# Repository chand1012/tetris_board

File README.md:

# Tetris Circuit Board
schemiatic and arduino file for a credit card sized tetris board.
## To do ##
- ~~Upload the .ino file~~
- add way to program atmega328p or add DIP Socket
- Finish the ~~Gerber~~ BOM File (Add all components to list, [this](https://octopart.com/bom-tool) should help.)
- have some printed and assembled by [Seeed](https://www.seeedstudio.com/fusion_pcb.html)
- figure out the switch you want to use on the boards
### Other assembly options ###
- Order the PCB from [Seeed](https://www.seeedstudio.com/fusion_pcb.html), assemble it yourself.

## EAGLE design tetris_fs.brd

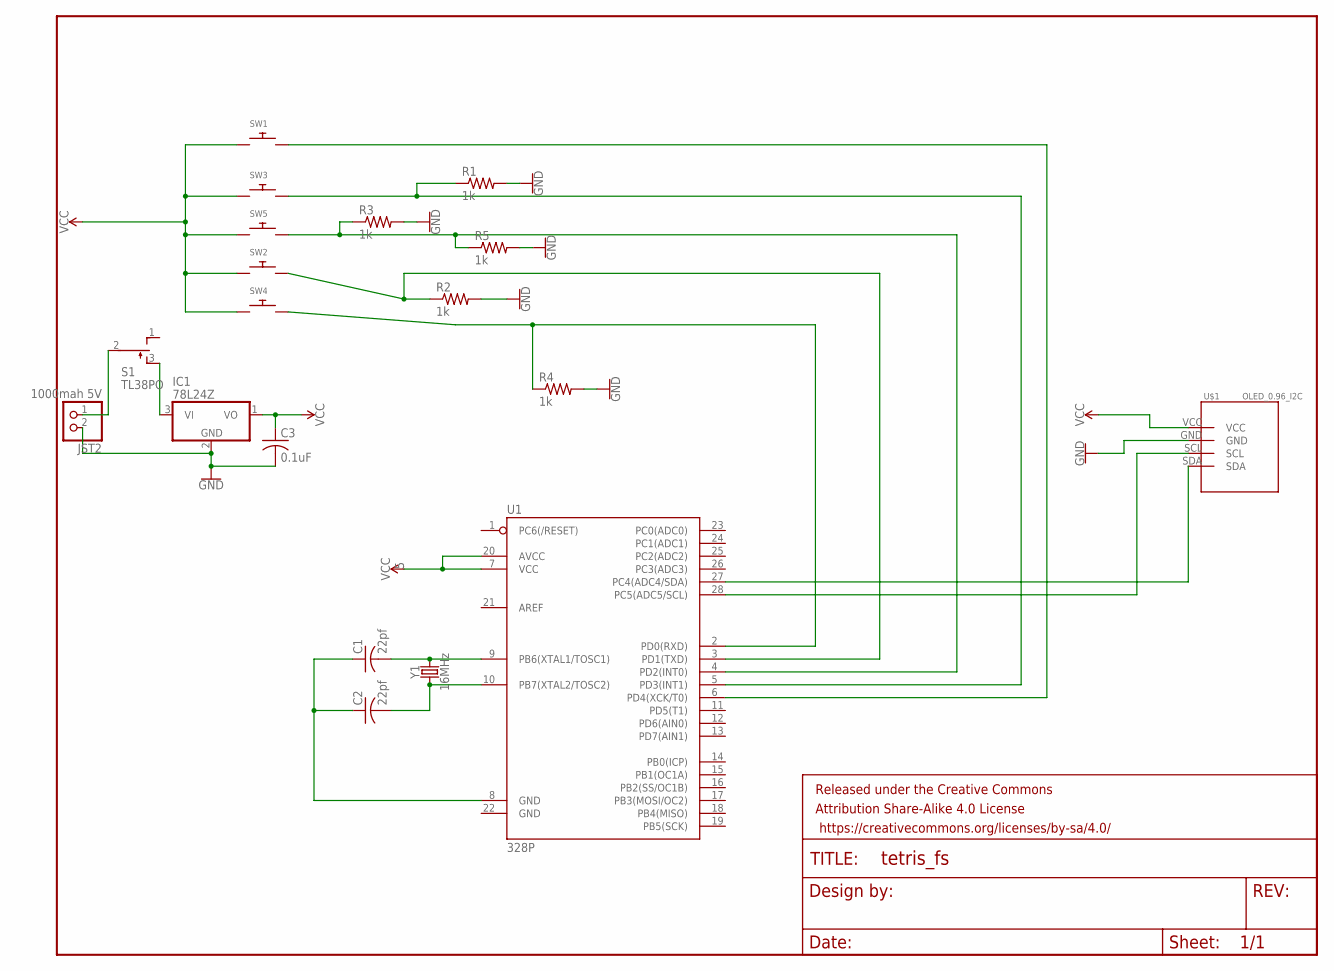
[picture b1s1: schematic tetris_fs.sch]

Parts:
C1, C2: 22pf; C050-030X075
C3: 0.1uF; C050-030X075
FRAME1: FRAME-LETTERNO_PACKAGE; DUMMY
IC1: 78L24Z; TO92
JST2: 1000mah 5V; JST-PH-2-SMT-RA
R1, R2, R3, R4, R5: 1k; 0805-THM
S1: TL38PO; TL3XPO
SW1, SW2, SW3, SW4, SW5: SWITCH_PUSHBUTTONC&K_KSS; BTN_CK_KSS
U1: 328P; DIP28
U$1: OLED_0.96_I2C
Y1: 16MHz; HC49US

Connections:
GND: C3.2, IC1.2 (GND), JST2.2 (1), R1.2, R2.2, R3.2, R4.2, R5.2, U$1.GND
unnamed: SW1.P$2, U1.6 (PD4(XCK/T0))
unnamed: R1.1, SW3.P$2, U1.5 (PD3(INT1))
unnamed: R3.1, R5.1, SW5.P$2, U1.4 (PD2(INT0))
unnamed: R2.1, SW2.P$2, U1.3 (PD1(TXD))
unnamed: R4.1, SW4.P$2, U1.2 (PD0(RXD))
unnamed: C1.2, U1.9 (PB6(XTAL1/TOSC1)), Y1.2
unnamed: C2.2, U1.10 (PB7(XTAL2/TOSC2)), Y1.1
unnamed: C1.1, C2.1, U1.8 (GND)
unnamed: JST2.1 (2), S1.2
unnamed: U1.27 (PC4(ADC4/SDA)), U$1.SDA
unnamed: U1.28 (PC5(ADC5/SCL)), U$1.SCL
unnamed: IC1.3 (VI), S1.3 (S)
VCC: C3.1, IC1.1 (VO), SW1.P$1, SW2.P$1, SW3.P$1, SW4.P$1, SW5.P$1, U1.7 (VCC), U1.20 (AVCC), U$1.VCC

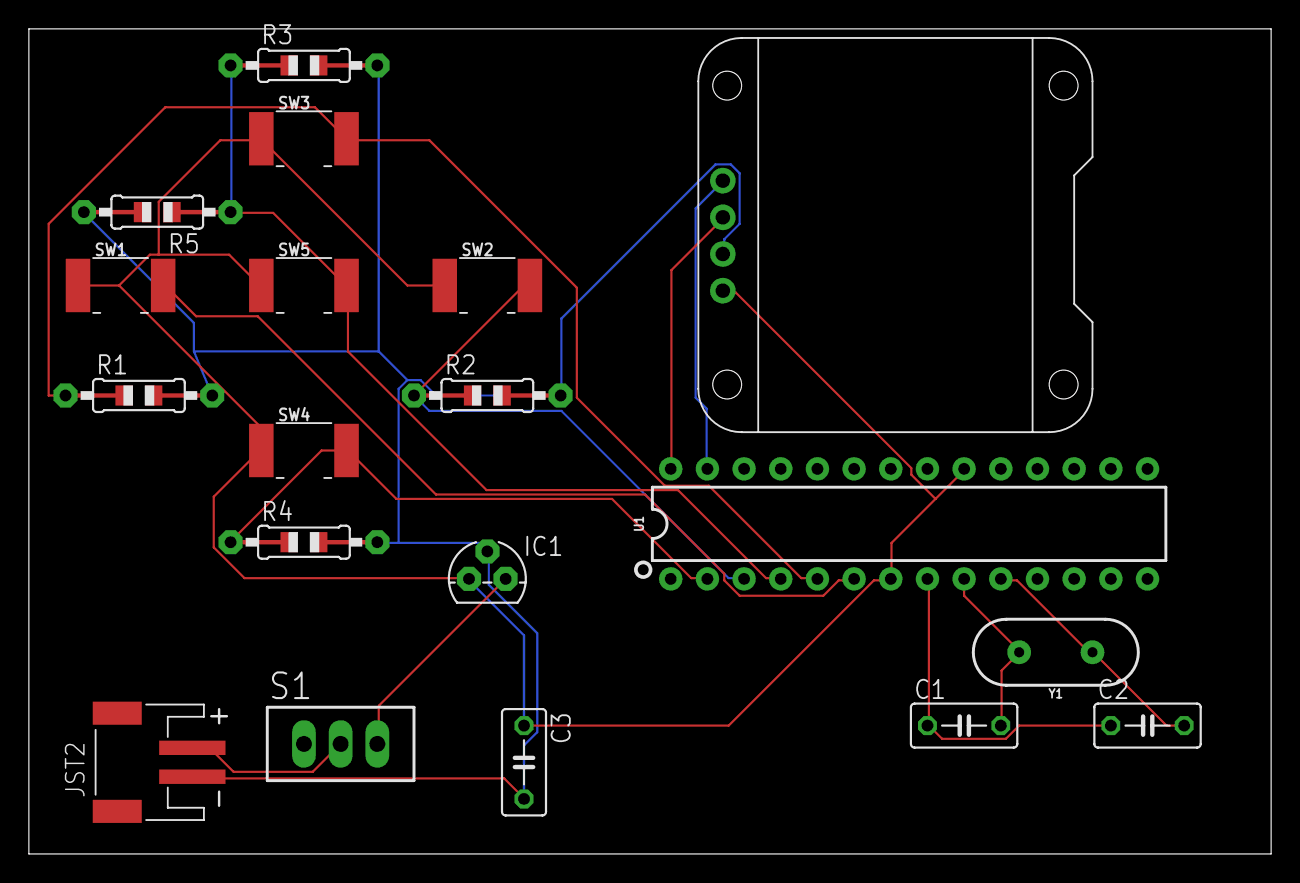
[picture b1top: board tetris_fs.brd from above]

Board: 2 copper layers, 86.0 x 57.1 mm, 20 parts (0 on the bottom side), 14 nets.

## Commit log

2017-10-14 added schematic and CAD files
2017-10-15 added ino, updated readme
2017-10-15 Added gitignore and autoroute
2017-10-15 added an on off switch
2017-10-15 edited readme
2017-10-17 Added full size resistor/capacitor version
2017-10-18 updated board layout, updated readme

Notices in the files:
parts and their libraries:
SparkFun-Aesthetics: Licensing: Creative Commons ShareAlike 4.0 International - https://creativecommons.org/licenses/by-sa/4.0
SparkFun-Aesthetics: Released under the Creative Commons Attribution Share-Alike 4.0 License
SparkFun-Aesthetics: https://creativecommons.org/licenses/by-sa/4.0
